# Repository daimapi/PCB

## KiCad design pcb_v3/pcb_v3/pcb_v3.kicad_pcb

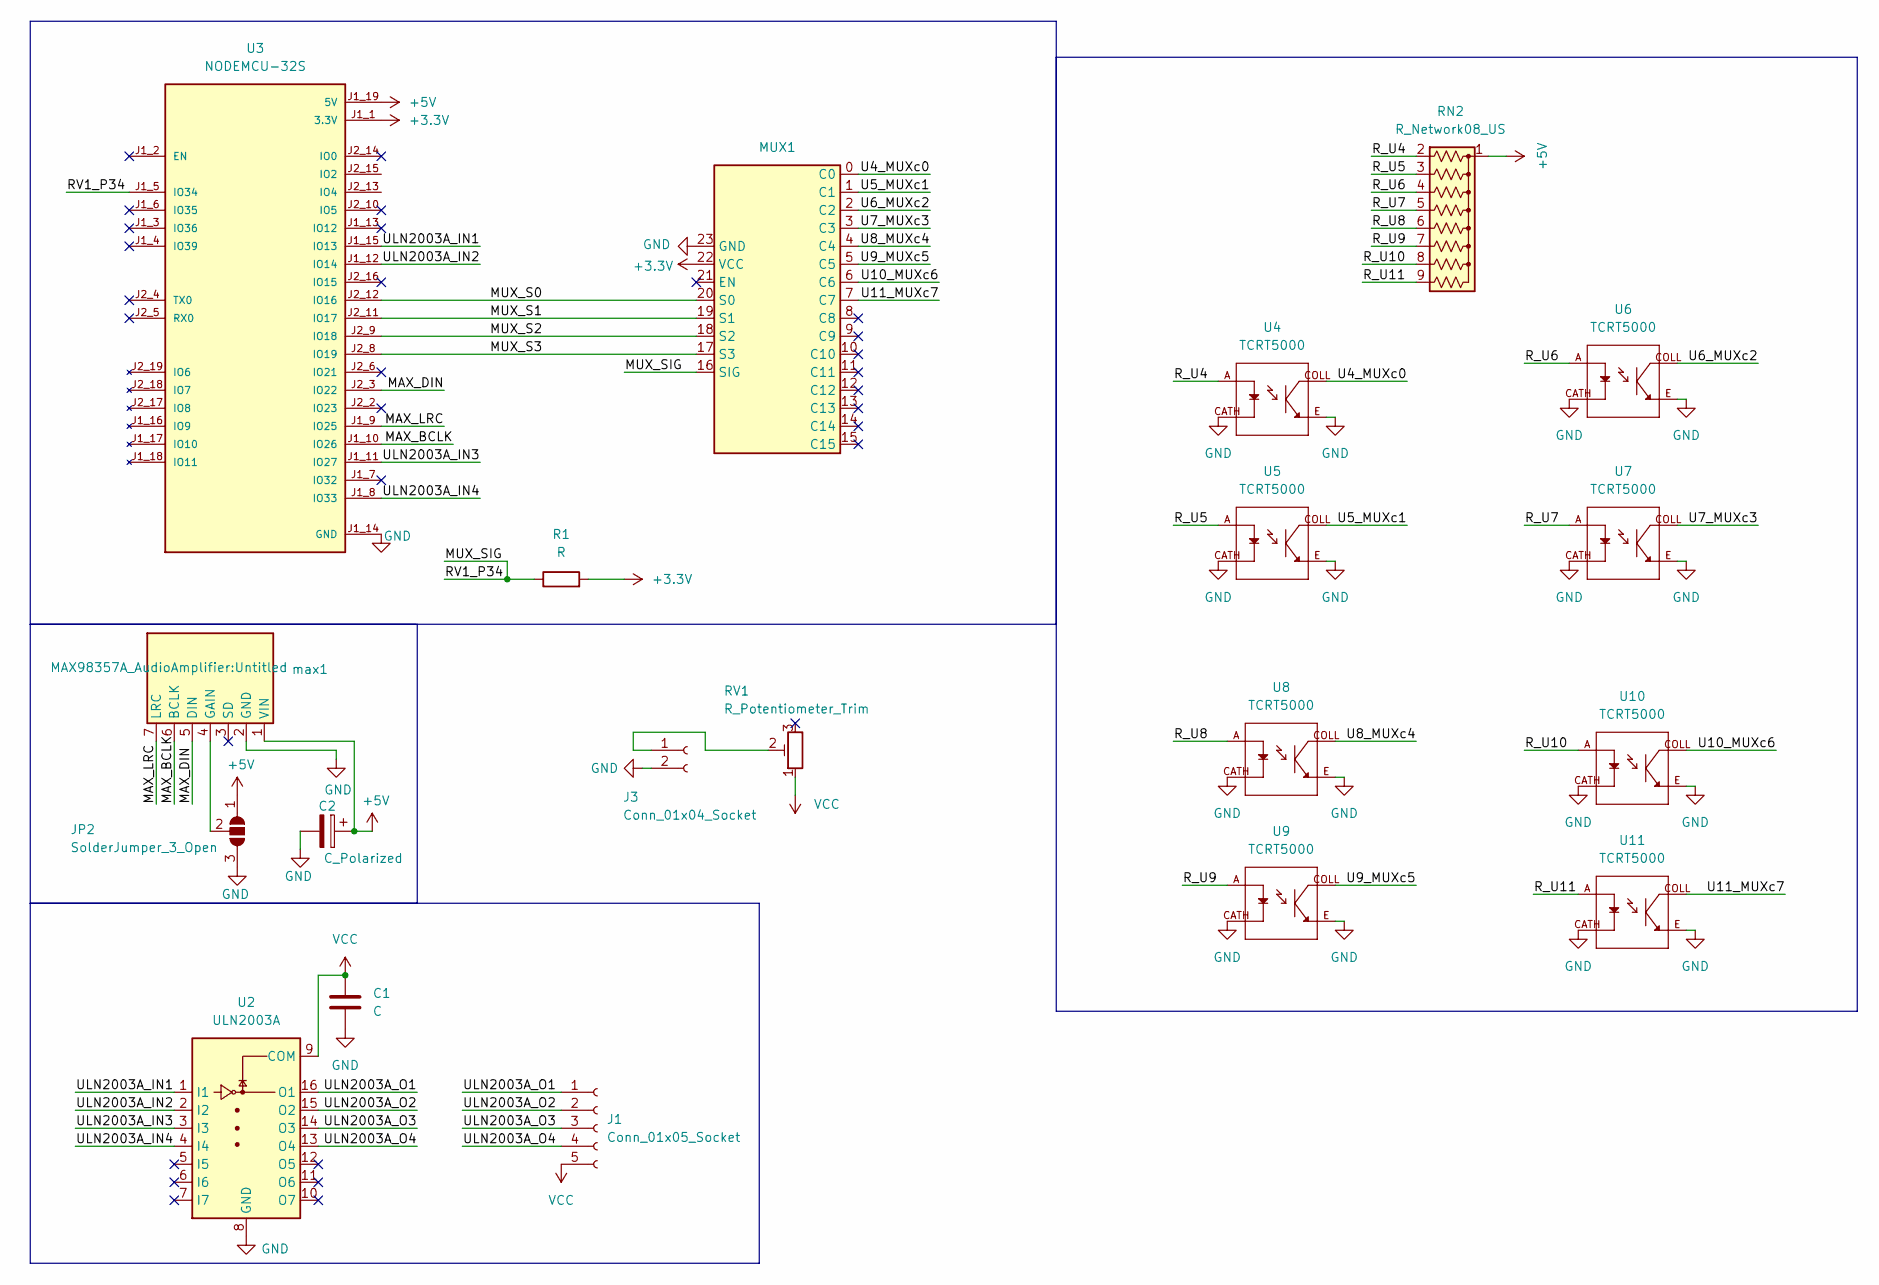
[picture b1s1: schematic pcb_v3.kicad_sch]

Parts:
C1: C; C_Disc_D6.0mm_W2.5mm_P5.00mm
C2: C_Polarized; CP_Radial_D7.5mm_P2.50mm
J1: Conn_01x05_Socket; Molex_KK-254_AE-6410-05A_1x05_P2.54mm_Vertical
J3: Conn_01x04_Socket; TerminalBlock_Phoenix_MKDS-1,5-2_1x02_P5.00mm_Horizontal
JP2: SolderJumper_3_Open; SolderJumper-3_P2.0mm_Open_TrianglePad1.0x1.5mm_NumberLabels
MUX1: 16to8mux
R1: R; R_Axial_DIN0309_L9.0mm_D3.2mm_P12.70mm_Horizontal
RN2: R_Network08_US; R_Array_SIP9
RV1: R_Potentiometer_Trim; Potentiometer_Bourns_3296X_Horizontal
U2: ULN2003A; DIP-16_W7.62mm
U3: NODEMCU-32S; MODULE_NODEMCU-32S; PARTREV V1
U4, U5, U6, U7, U8, U9, U10, U11: TCRT5000; OPTO_TCRT5000; PARTREV 1.7
max1: Untitled

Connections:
+3.3V: MUX1.22 (VCC), R1.2, U3.J1_1 (3.3V)
+5V: C2.1, JP2.1 (A), RN2.1 (common), U3.J1_19 (5V), max1.1 (VIN)
/MAX_BCLK: U3.J1_10 (IO26), max1.6 (BCLK)
/MAX_DIN: U3.J2_3 (IO22), max1.5 (DIN)
/MAX_LRC: U3.J1_9 (IO25), max1.7 (LRC)
/MUX_S0: MUX1.20 (S0), U3.J2_12 (IO16)
/MUX_S1: MUX1.19 (S1), U3.J2_11 (IO17)
/MUX_S2: MUX1.18 (S2), U3.J2_9 (IO18)
/MUX_S3: MUX1.17 (S3), U3.J2_8 (IO19)
/MUX_SIG: MUX1.16 (SIG), R1.1, U3.J1_5 (IO34)
/R_U4: RN2.2 (R1), U4.A
/R_U5: RN2.3 (R2), U5.A
/R_U6: RN2.4 (R3), U6.A
/R_U7: RN2.5 (R4), U7.A
/R_U8: RN2.6 (R5), U8.A
/R_U9: RN2.7 (R6), U9.A
/R_U10: RN2.8 (R7), U10.A
/R_U11: RN2.9 (R8), U11.A
/U4_MUXc0: MUX1.0 (C0), U4.COLL
/U5_MUXc1: MUX1.1 (C1), U5.COLL
/U6_MUXc2: MUX1.2 (C2), U6.COLL
/U7_MUXc3: MUX1.3 (C3), U7.COLL
/U8_MUXc4: MUX1.4 (C4), U8.COLL
/U9_MUXc5: MUX1.5 (C5), U9.COLL
/U10_MUXc6: MUX1.6 (C6), U10.COLL
/U11_MUXc7: MUX1.7 (C7), U11.COLL
/ULN2003A_IN1: U2.1 (I1), U3.J1_15 (IO13)
/ULN2003A_IN2: U2.2 (I2), U3.J1_12 (IO14)
/ULN2003A_IN3: U2.3 (I3), U3.J1_11 (IO27)
/ULN2003A_IN4: U2.4 (I4), U3.J1_8 (IO33)
/ULN2003A_O1: J1.1, U2.16 (O1)
/ULN2003A_O2: J1.2, U2.15 (O2)
/ULN2003A_O3: J1.3, U2.14 (O3)
/ULN2003A_O4: J1.4, U2.13 (O4)
GND: C1.2, C2.2, J3.2, JP2.3 (B), MUX1.23 (GND), U2.8 (GND), U3.J1_14 (GND), U3.J2_1 (GND), U3.J2_7 (GND), U4.CATH, U4.E, U5.CATH, U5.E, U6.CATH, U6.E, U7.CATH, U7.E, U8.CATH, U8.E, U9.CATH, U9.E, U10.CATH, U10.E, U11.CATH, U11.E, max1.2 (GND)
unnamed: J3.1, RV1.2
unnamed: JP2.2 (C), max1.4 (GAIN)
VCC: C1.1, J1.5, RV1.1, U2.9 (COM)

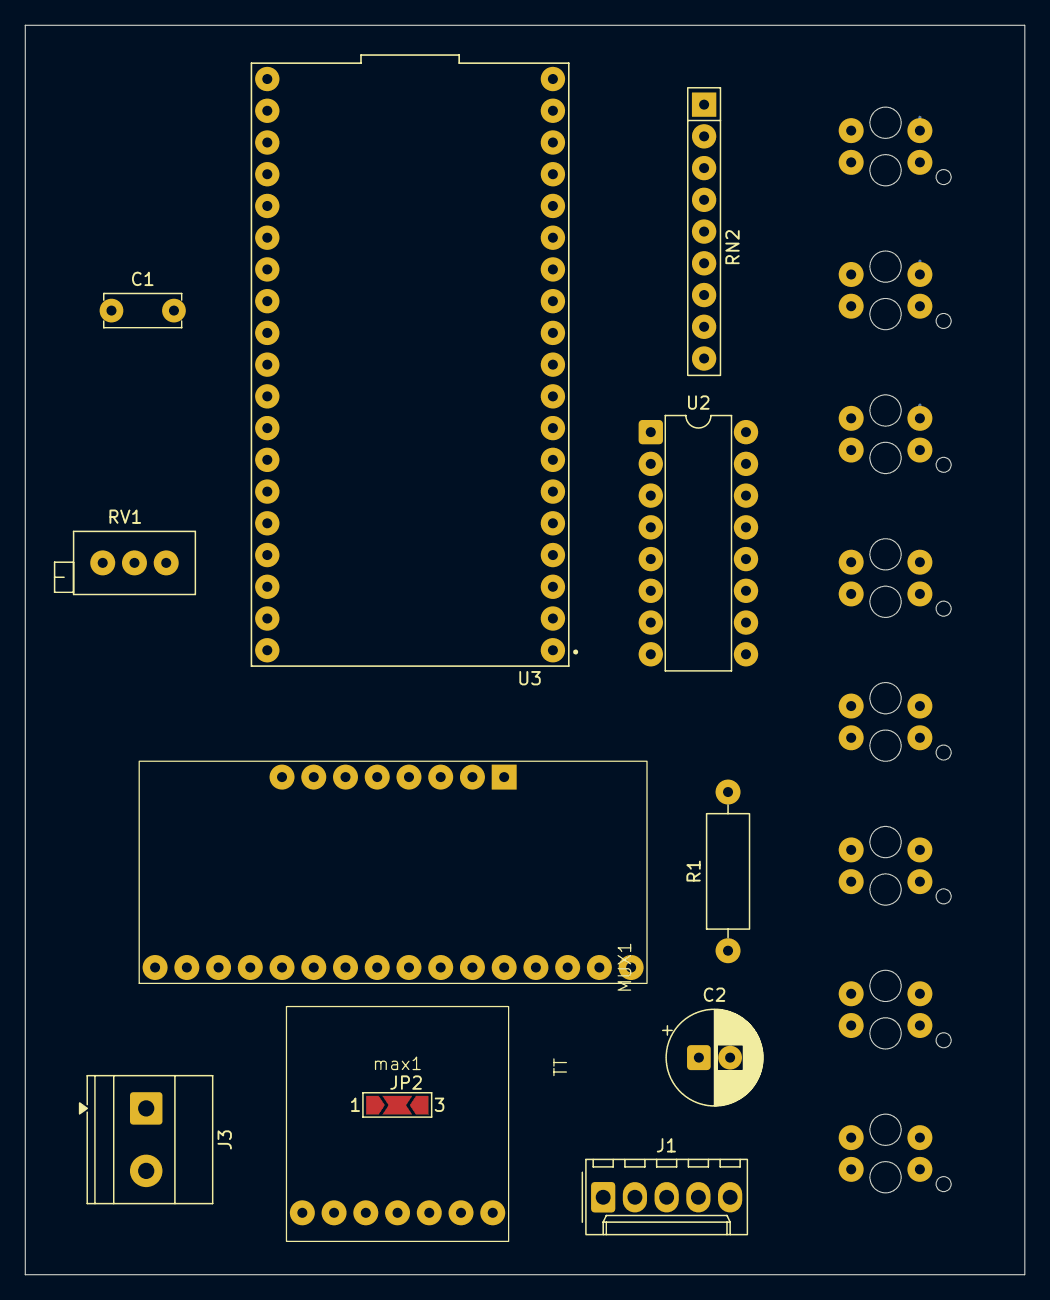
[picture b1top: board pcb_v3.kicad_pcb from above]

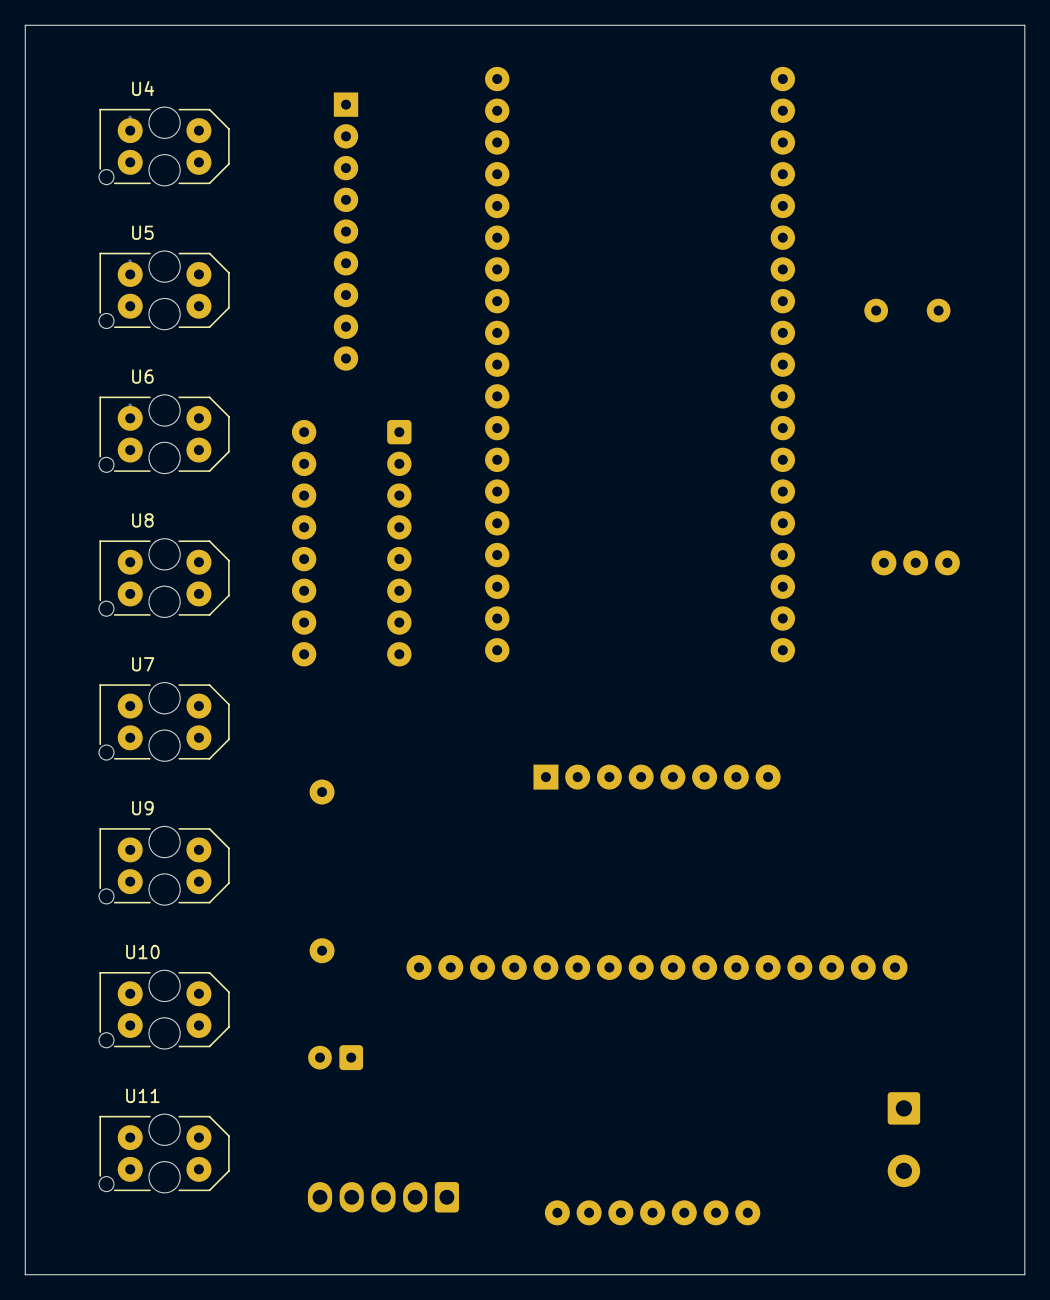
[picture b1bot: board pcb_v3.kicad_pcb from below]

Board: 2 copper layers, 80.0 x 100.0 mm, 20 parts (8 on the bottom side), 38 nets.

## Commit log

2026-05-20 Add files via upload
    ///v3 prog.
    scheme done
    yet to finish pcb layout
    ///changes from v2
    added battery vin
    R_Variant (potentiometer)
2026-05-21 shouldn't be v3 but pcb scheme final chk ver
2026-05-21 done all footprint
2026-05-21 wrong tcrt wiring
2026-06-12 1.delete useless pins in sch and layout 2.rewire potentiometer to vcc, enable us to modify voltage input for motor, preventing fast-battery run out. original wire(mux_sig) is now wired to 3.3v 3.pin9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
2026-06-12 1.linbf said tcrt Collector needs a 440ohm res., so i add a res. 2.i have modify the pads in the pcb to 1.95~2mm (depends on hole spaceing differences in diffierent footprints) and hole to 0.8mm
